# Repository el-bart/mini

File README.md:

mini
====

repo for mini-projects (one-filers, etc...).

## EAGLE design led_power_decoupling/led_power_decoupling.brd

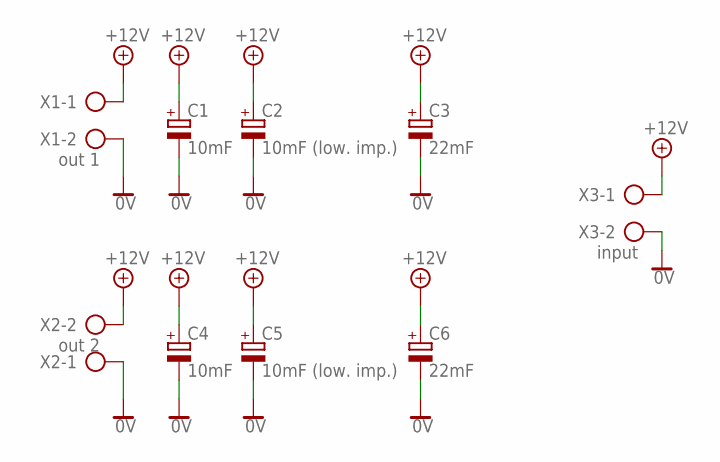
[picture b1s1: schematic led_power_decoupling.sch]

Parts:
C1, C4: 10mF; E7,5-16
C2, C5: 10mF (low. imp.); E7,5-18
C3, C6: 22mF; EB25D
X1: out 1; AK500/2
X2: out 2; AK500/2
X3: input; AK500/2

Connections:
0V: C1.-, C2.-, C3.-, C4.-, C5.-, C6.-, X1.2, X2.1, X3.2
+12V: C1.+, C2.+, C3.+, C4.+, C5.+, C6.+, X1.1, X2.2, X3.1

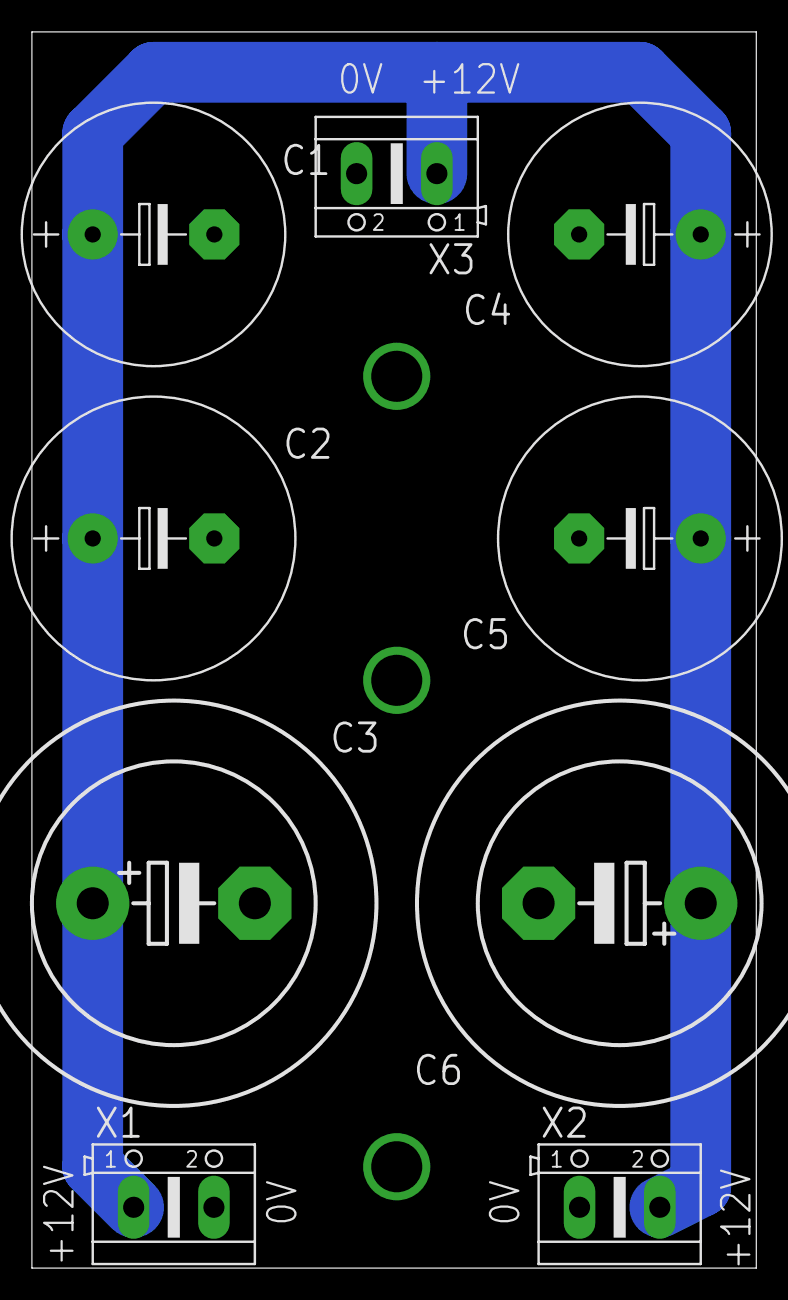
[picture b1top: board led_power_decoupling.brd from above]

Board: 2 copper layers, 45.4 x 77.5 mm, 9 parts (0 on the bottom side), 2 nets.

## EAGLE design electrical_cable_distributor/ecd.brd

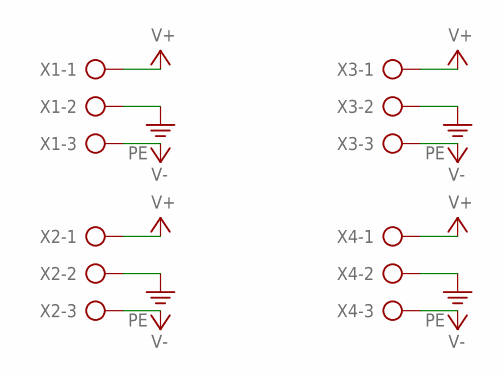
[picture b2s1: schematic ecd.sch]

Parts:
X1, X2, X3, X4: AK500/3

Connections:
PE: X1.2, X2.2, X3.2, X4.2
V+: X1.1, X2.1, X3.1, X4.1
V-: X1.3, X2.3, X3.3, X4.3

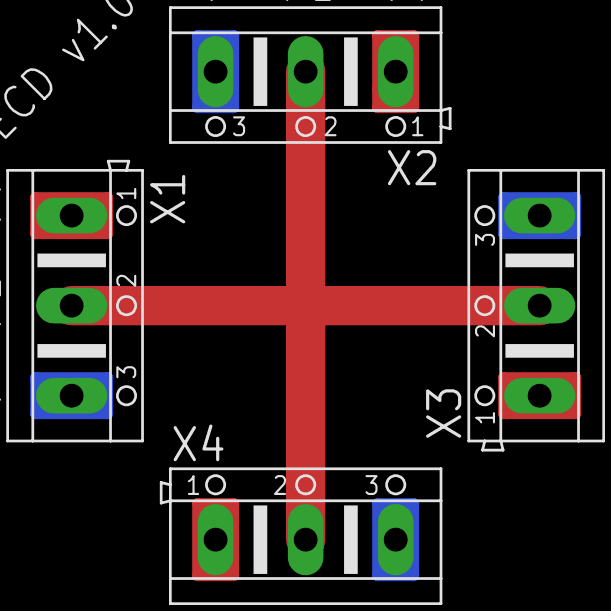
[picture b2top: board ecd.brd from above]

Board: 2 copper layers, 4 parts (0 on the bottom side), 3 nets.

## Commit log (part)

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2025-12-07 LED simplified
2025-12-07 watchdog set yo 8s
2025-12-07 back to 120ms
2025-12-07 adjsutements after changing namespaces
2025-12-07 SwPWM draft
2025-12-07 PoC with 50% duty cycle
2025-12-07 removed unused param
2025-12-07 helper scritp for computing gamma-correction LUT for AVR
2025-12-07 added fade in and out to main
2025-12-07 fade in and out impl. for LED::State + some compile-time constants to play with
2025-12-07 renamed LUT generator + added nicer formatting
2025-12-07 added custom cycle for on/off-s
2025-12-07 cycles are now generated using rand()
2025-12-08 added code generation for LUT
2025-12-08 using generated code now
2025-12-08 added PRNG seeded based on EEPROM, to save some entropy
2025-12-08 keeping seed as unsigned to avoid flipping signed values
2025-12-09 there's s macro for wairing for write to complete
2025-12-09 added C++ compliant number to pointer conversion
2025-12-09 working read-write example
2025-12-09 compile / flash / read hex scripts
2025-12-09 * fixed PRNG state saving * removed test / PoC code for EEPROM from main()
2025-12-09 moved compile time constant to a place where it's actually used
2025-12-09 more cannonical init
2025-12-21 xmass light mounts on a balkony - 3D SDK
2025-12-21 project description
2025-12-21 PET-G/waterproof
2025-12-21 corner hook design
2025-12-21 printing 10x at a time
2025-12-21 moved corner-hook-specific param to the model file
2025-12-21 prototype for a balcony hook
2025-12-21 6x books
2025-12-21 added rim around for some extra stiffness
2025-12-21 removed bottom notch
2025-12-21 adjusted printing parameters for easier printing
2025-12-29 added description of the repo
2025-12-29 3D SDK for camera mount
2025-12-29 1st draft of the mount base
2025-12-29 adjusted sizes, and rotated to for print orientation
2025-12-29 0.3mm layer height, as we're mor interested in speat than precision here
2025-12-29 added camera holder itself
2025-12-29 added Wayland forwardinf for steam (WIP)
2025-12-29 added missing libs for Vulkan and Mesa
2025-12-29 * added wayland forwarding * added steam flags to run non-sandboxed CEF
2025-12-29 steam bumped to debian:13 + added missing tools for Vulkan
2025-12-29 3D SDK for multiple marker holders for whiteboard
2025-12-29 multi-marker holder
2025-12-29 added some nice touches to make print easier to handle
2025-12-29 bed temperature down to 60°C for PLA/Silk
2026-01-01 added Xwayland for image
2026-01-01 WIP for Wayland
2026-01-01 removed Wayland testing code
2026-01-01 Wayland note
2026-01-01 fixed comment
2026-01-10 3D SDK for digital hourglass
2026-01-10 trigger board enc for USB-C added as a helper model
2026-01-10 added hourglass box
2026-01-11 draft of CubicSDR
2026-01-11 WIP...
2026-01-11 fixed SDR device access
2026-01-11 fixed path to dockerfile, when not running from a local dir
2026-01-11 3D SDK for AVT's dusk sensor
2026-01-11 USB-C trigger board
2026-01-11 dusk switch box
2026-01-11 added LED support strip, to make connection more firm (yes, it's not part of the set, but it's how my kids use it - so there u have it... ;))
2026-01-12 3D SDK for toy rocket cone
2026-01-12 model of the nose cone
2026-01-12 print settings a bit more optimized for speed
2026-01-14 3D SDK for laptop holder for the desk
2026-01-14 PET-G/strength
2026-01-14 holder for a laptop, attached to a desk
2026-01-14 no infill plz
2026-01-14 rpitning 2 copies at a time
2026-01-14 ajudsted sizes for more strength
2026-01-18 dehydration pipe holder for A/C unit
2026-01-18 A/C dehydration pipe holder
2026-01-23 f-14 moved to ext, as this is where it belongs
2026-01-30 3D SDK for flowerpot for Grzybek
2026-01-30 flowerpot sourcer added
2026-01-30 renamed file
2026-01-30 flowerpot itself
2026-01-30 25% PCF for surface quality
2026-01-31 added 1 more hole in the center
2026-01-31 adjusted size of side-balls to finish print faster
2026-02-03 yt-dlp wrapper running inside docker
2026-02-03 yt-dlp-docker description
2026-02-03 * added checking of the checksum of the downloaded archive * moved version and hash to a variable at the top of the file
2026-02-03 constants are now marged as readonly
2026-02-03 added ffmpeg for merging A+V files
2026-02-11 copilot-cli wrapper for docker
2026-02-11 simplified script and mounting rules
2026-02-11 whitelisting less by default
2026-02-14 3D SDK
2026-02-14 print solid
2026-02-14 box for random PCB for kids
2026-02-15 toy barrel plug ending
2026-02-15 non-scarf seam
2026-02-15 addjusted sizings and speeds
2026-02-15 steam-xwayland added
2026-02-25 yt-dlp bumped to 2026.02.21
2026-02-25 crontab might not always set USER
2026-02-28 new GPG key from steam
2026-03-07 nower yt-dlp with nodejs for JS code
2026-03-08 data and installer dirs
2026-03-08 base image for gaming
2026-03-08 scripts for gaming
2026-03-08 preventing network access for the container
2026-03-08 KSP installer bacame a base for dockerized linux games
2026-03-08 passing all the params down the chain
2026-03-08 added missing flag to run cmd with args under xterm
2026-03-08 template ./play script to be customized to run a game of chice
2026-03-08 brief project description
2026-03-28 3D SDK for hairdryer hook
2026-03-28 PLA / strength
2026-03-28 hairdryer hook
2026-03-28 simpler infill for faster printing
2026-03-28 2 hooks per hairdryer
2026-03-28 3D SDK for toy coil
2026-03-28 toy coil cap
2026-03-29 3D SDK for toy 3D lock box
2026-03-29 3-digit lock box model
2026-04-05 toy_3_digit_lock_box moved to ext. 3D projects, where it belongs
2026-04-09 newer yt-dlp
2026-04-22 3D SDK for toy relay box light
2026-04-22 wrap around the toy relay box for light
2026-04-24 3D SDK for colorful vase
2026-04-24 Silk/vase
2026-04-24 3D SDK bugfix
2026-04-24 printing thicker layers
2026-04-24 rainbow silk vase model
2026-04-24 added more precise rendering, for improved quality
2026-04-24 1st layers are to be more precise
2026-04-24 3D SDK - more tunning
2026-04-25 SR-71 model stand - 3D SDK
2026-04-25 model's base, to be installed on the LCD
2026-04-25 printing all in PLA + model of the mount itself
2026-04-25 added a bit steeper mount, for better outlook
2026-04-25 SR-71 model link added to stand
2026-04-30 SDK for rp2040
2026-04-30 added example app
2026-04-30 rp2040 demo app
2026-04-30 servo handling class
2026-04-30 added missing PWM-enable
2026-04-30 removed dead code for pin init
2026-04-30 2x servo experiment
2026-04-30 added structure to move all servos in tandem
2026-04-30 added ADC helper
2026-04-30 integreated ADC-to-servo position loop
2026-05-10 night of snow - model base
2026-05-10 night of snow - base model added
2026-05-10 asimo robot print in place - 3D SDK
2026-05-10 asimo robot print in place - model
2026-05-14 3D SDK for bike flag holder
2026-05-16 added some extra space on top for the screw's head
2026-05-18 3D SDK for enclosure for joystick
2026-05-18 back to PLA
2026-05-18 electronics box
2026-05-18 removed object highlighting
2026-05-28 game: KSP linux startup env
2026-05-28 game: TA linux startup env
2026-06-05 3D SDK for toy rocket shape
2026-06-05 body
2026-06-05 added cone part
2026-06-05 rocket is now a bit bigger and in 3 parts for faster print
2026-06-06 door knob's bistable block - 3D SDK
2026-06-06 3D SDK bump with TPU/solid profile
2026-06-06 TPU40D/solid
2026-06-06 project's description
2026-06-06 bistable door block - 1st draft
2026-06-06 thicker bounce + moved a bit lower to not interfere with top block
2026-06-06 generally avoid crossing perimeters for TPU, due to quality concerns
2026-06-06 going for higher layer height, to speed up the print
2026-06-06 label added to explain why larger layer lines
2026-06-06 new, triangle-based blocking corner approach + adjusted certain params
2026-06-06 replaced triangular shape with a simple hook
2026-06-06 slowed down a bit
2026-06-07 added booster to the print
2026-06-07 delfinki: thank you photo box - 3D SDK
2026-06-07 exterior - box's cover
2026-06-07 added nicer roundings
2026-06-07 added rough visualization of the bottom part
2026-06-07 top part of the box - WIP
2026-06-07 higher cut
2026-06-07 happy dolphin - vector graphics
2026-06-07 image slightly tweaked for better printing
2026-06-07 fixed SVG so that it forms a closed geometry
2026-06-07 added 'happy dolphin' engraving on the lid
2026-06-07 fixed box's h - the box_cut_edge_h is an overlap here
2026-06-08 printing in Silk/none + some quality-related modifications
2026-06-08 decreased amount of space for photos - turned out that the stack won't be that high
2026-06-08 added Z-cut for top and bottom layers
2026-06-08 added space for fingers, to be able to open the box conveniently
2026-06-08 added better positioning (in case of 2-in-1 printing)
2026-06-08 fingers cut-in depth adjusted
2026-06-08 added magnet slots on both sides
2026-06-08 added extra clearance on the top, to ensure box's lid won't wobble
2026-06-08 added explicit param to designate how deep the magnets should be burried
2026-06-09 added photodeck visualization
2026-06-09 added TODO for a future edition(s)
2026-06-10 dyzio wełniak - dir + readme
2026-06-10 dyzio wełniak - 3D SDK
2026-06-10 gabit
2026-06-10 3D SDK bump
2026-06-16 updated yt-dlp
2026-06-20 toy money box
2026-06-20 body of the main box
2026-06-20 main box is ready
2026-06-20 * added cover part * decreased height of the model
2026-06-20 * thicker wall * wider
2026-06-21 3D SDK for cooling duct adapter
2026-06-21 fan ring - test adapter / print
2026-06-21 renamed vars for fan_*
2026-06-21 added test duct print part
2026-06-21 for pipe-adapter we have fixed ext-diameter
2026-06-21 improved printing characteristics
2026-06-21 full funnel / adapter part
2026-06-21 0.3mm layer height for laster printing
2026-06-21 1st layer 0.3mm as well
2026-06-21 draft of the adapter holder tooth
2026-06-21 4 units at a time
2026-06-30 3D SDK for USB snd card holder
2026-06-30 USB card holder with 5x5mm cylindrical magnets
2026-06-30 project info
2026-06-30 * added air vent hole for magnet insertion * fixed wing size * decreased spacing for a tighter fit
